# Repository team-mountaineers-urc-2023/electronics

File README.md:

# Electronics
This repository contains diagrams of Wanderer's electrical systems as well as PCBs designed by the Electronics sub-team.

# Table of Contents
[Downloading the Repository](#downloading-the-repository)   
[Required Software](#required-software)  
[Repository Contents](#repository-contents)  

# Downloading the Repository
## Pre-Install: SSH Key
An ssh key for your current machine must be added to your Github account to clone our repositories.  
SSH keys are used for passwordless authentication.  
For more information see https://docs.github.com/en/authentication/connecting-to-github-with-ssh.

## Creating an SSh Key
`$ ssh-keygen`  
Keep the default file name, add a password if you'd like. 

## Adding the SSH Key to your Github account
Go to https://github.com/settings/keys and click "New SSH Key"  
The title can be anything.  
For Key, copy paste the output of `$ cat ~/.ssh/id_rsa.pub`

## Clone the workspace
Install git if not done so already with `$ sudo apt install git` then:  
`git clone git@github.com:team-mountaineers-urc-2023/electronics.git ~electronics`
* If this is your first time talking to Github on your machine, you will receive a warning saying authenticity cannot be established.  
	Type "yes" and hit enter.

# Required Software
Block diagrams and schematics can be viewed using any PDF viewer.
All PCBs were designed using KiCad 7.0. The most recent version of the software can be downloaded at https://www.kicad.org/download/.

# Repository Contents

## System Schematics

Main Electronics Box Diagram

Manipulator Electronics Diagram

Science Electronics Diagram

## PCB Files

Battery Monitor v1.2

Payload PCB v3.1

Power Distribution Board

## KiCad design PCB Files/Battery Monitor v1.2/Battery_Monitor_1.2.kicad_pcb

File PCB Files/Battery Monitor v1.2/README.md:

# Battery Monitor v1.2

## Overview
The battery monitor was designed for the 2023 rover to monitor its battery usage. The PCB features shunt resistors to measure the current draw from up to four batteries. It can communicate status using an LCD screen or over the rover's CAN bus.

## Features
- 4-layer board
- Raspberry Pi Pico microcontroller
- Measures battery voltage and current using shunt resistors combined with LTC4151 ICs
- Embedded emergency stop circuitry
- Ideal diode circuits to connect batteries in parallel
- Control for an external LCD screen and an LED strip
- Hardware for CAN bus communication
- Reverse polarity protection

## Contributors
- [Kendra Gillo](https://github.com/kgillo)

- [Zach Waddell](https://github.com/zmw0006)

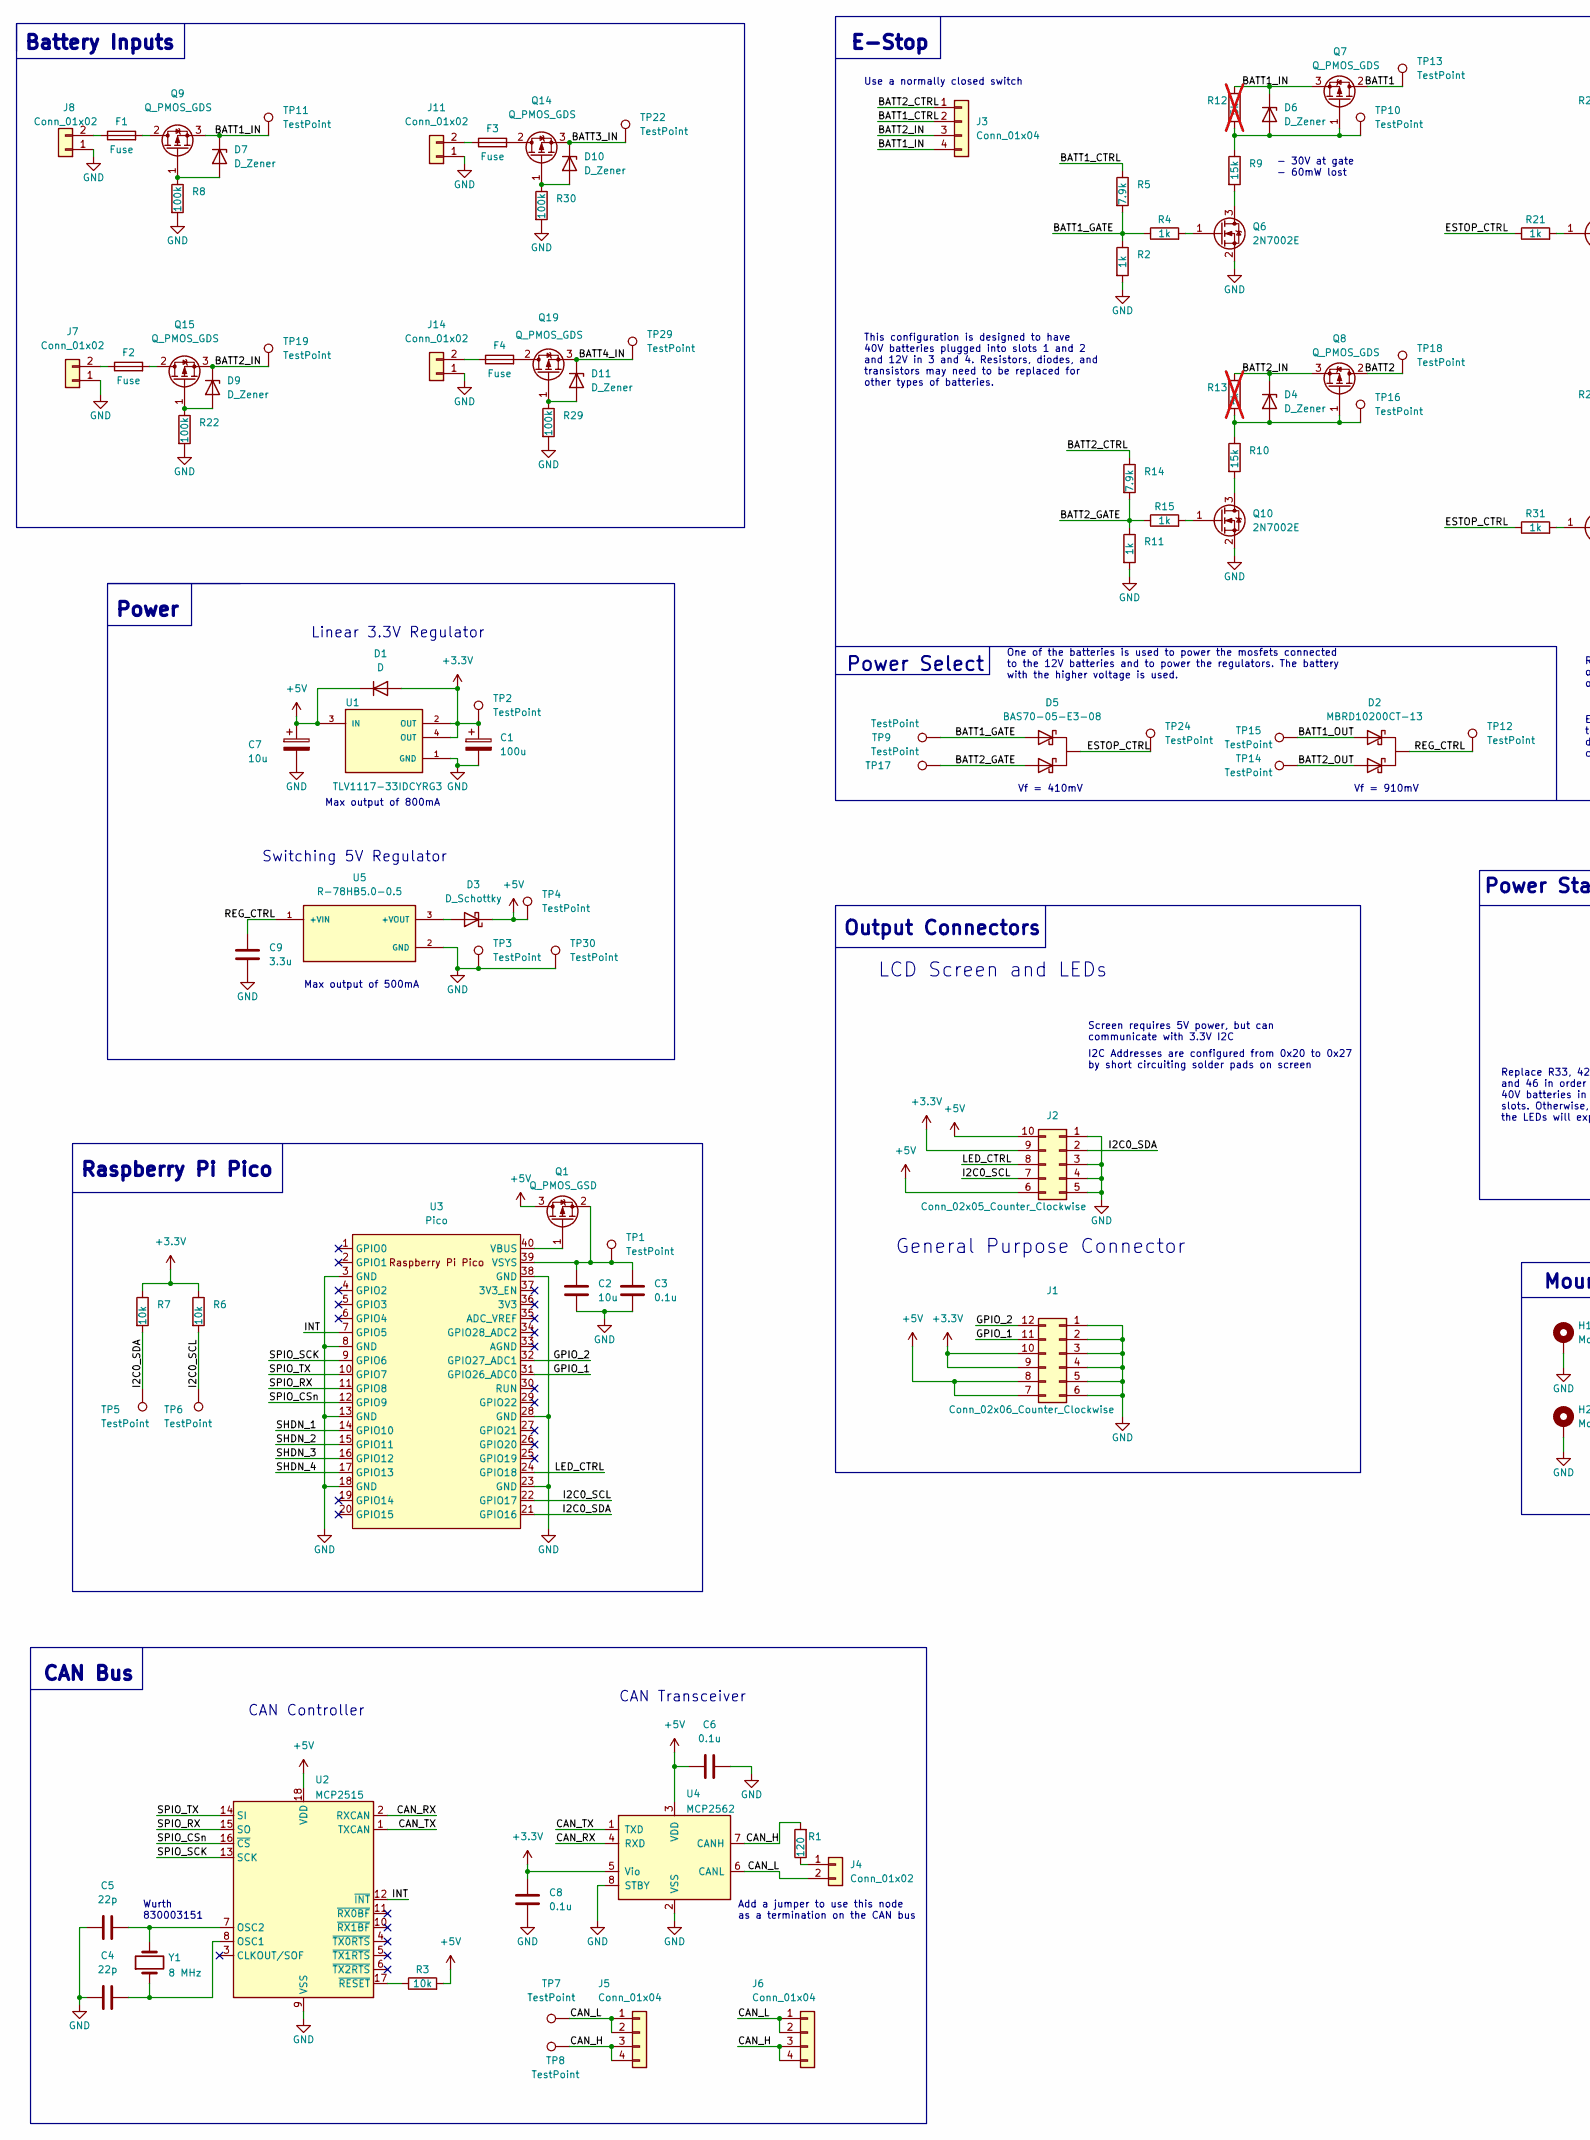
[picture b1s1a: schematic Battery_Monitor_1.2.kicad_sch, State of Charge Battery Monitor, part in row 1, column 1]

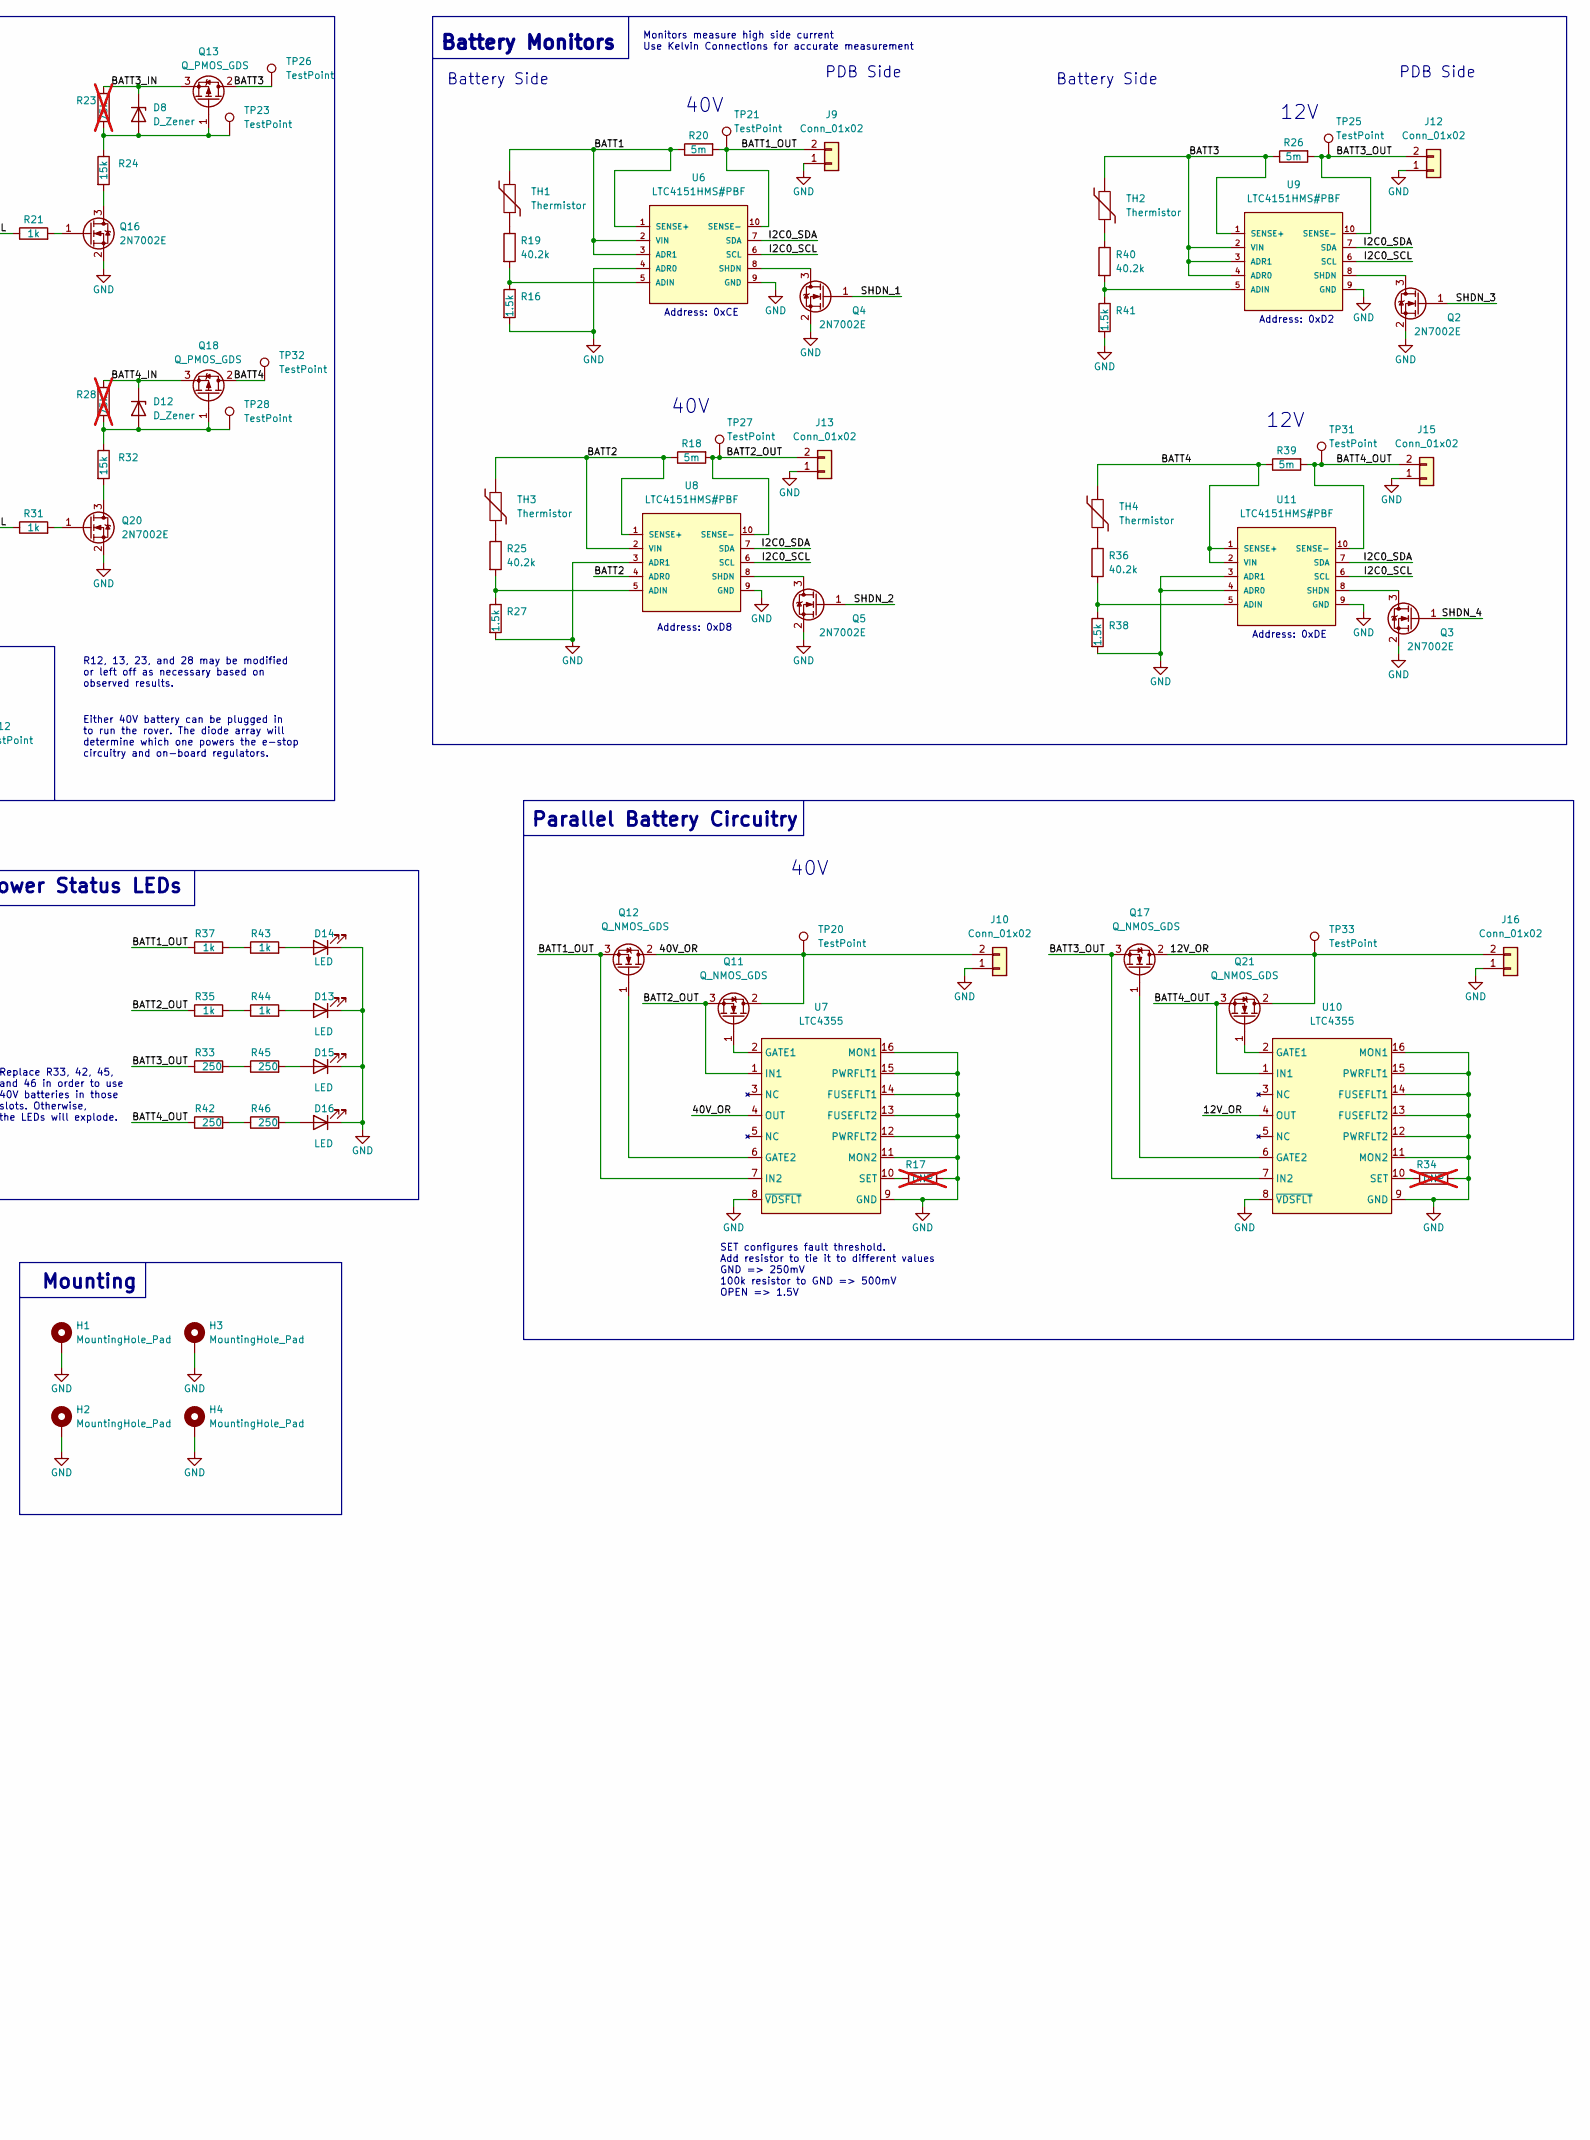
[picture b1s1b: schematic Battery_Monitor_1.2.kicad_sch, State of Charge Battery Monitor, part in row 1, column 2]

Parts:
C1: 100u; 1411 (3528 Metric)
C2, C7: 10u; C_0805_2012Metric_Pad1.18x1.45mm_HandSolder
C3: 0.1u; C_1206_3216Metric_Pad1.33x1.80mm_HandSolder
C4, C5: 22p; C_0603_1608Metric_Pad1.08x0.95mm_HandSolder
C6, C8: 0.1u; C_1206_3216Metric_Pad1.33x1.80mm_HandSolder; MANUFACTURER_PART_NUMBER 1206B104J500CT
C9: 3.3u; C_1812_4532Metric_Pad1.57x3.40mm_HandSolder
D1: D; SOD123FL3; MANUFACTURER_PART_NUMBER GS1001FL_R1_00001
D2: MBRD10200CT-13; TO-252-2; MANUFACTURER_PART_NUMBER MBRD10200CT-13
D3: D_Schottky; D_SOD-323; MANUFACTURER_PART_NUMBER CUS08F30,H3F
D4, D6, D7, D8, D9, D10, D11, D12: D_Zener; D_SOD-123; MANUFACTURER_PART_NUMBER BZT52C10-TP
D5: BAS70-05-E3-08; SOT-23; MANUFACTURER_PART_NUMBER BAS70-05-E3-08
D13, D14, D15, D16: LED; D_0805_2012Metric_Pad1.15x1.40mm_HandSolder; MANUFACTURER_PART_NUMBER LTST-C171GKT
F1, F2, F3, F4: Fuse; FUSE_3568
H1, H2, H3, H4: MountingHole_Pad; MountingHole_3.2mm_M3_DIN965_Pad
J1: Conn_02x06_Counter_Clockwise; Molex_Mini-Fit_Jr_5566-12A_2x06_P4.20mm_Vertical; MANUFACTURER_PART_NUMBER 0039281123
J2: Conn_02x05_Counter_Clockwise; Molex_Mini-Fit_Jr_5566-10A_2x05_P4.20mm_Vertical
J3: Conn_01x04; Molex_Mega-Fit_76829-0104_2x02_P5.70mm_Vertical; MANUFACTURER_PART_NUMBER 76829-0104
J4: Conn_01x02; PinHeader_1x02_P2.54mm_Vertical
J5, J6: Conn_01x04; 2604-3102; MANUFACTURER_PART_NUMBER 2604-3102
J7, J8, J9, J10, J11, J12, J13, J14, J15, J16: Conn_01x02; MOLEX_768290102; MANUFACTURER_PART_NUMBER 768290102
Q1: Q_PMOS_GSD; SOT-23; MANUFACTURER_PART_NUMBER DMG2305UX-13
Q2, Q3, Q4, Q5, Q6, Q10, Q16, Q20: 2N7002E; SOT-23; MANUFACTURER_PART_NUMBER 2N7002E
Q7, Q8, Q9, Q13, Q14, Q15, Q18, Q19: Q_PMOS_GDS; TO-252-2; MANUFACTURER_PART_NUMBER SUD50P10-43L-GE3
Q11, Q12, Q17, Q21: Q_NMOS_GDS; TO-252-2; MANUFACTURER_PART_NUMBER FDD86367
R1: 120; R_0805_2012Metric_Pad1.20x1.40mm_HandSolder; MANUFACTURER_PART_NUMBER CFR25SJT-52-120R
R2, R4, R11, R15, R21, R31, R35, R37, R43, R44: 1k; R_0805_2012Metric_Pad1.20x1.40mm_HandSolder
R3, R6, R7: 10k; R_0805_2012Metric_Pad1.20x1.40mm_HandSolder; MANUFACTURER_PART_NUMBER RNCP0805FTD10K0
R5, R14: 7.9k; R_0805_2012Metric_Pad1.20x1.40mm_HandSolder
R8, R22, R29, R30: 100k; R_0805_2012Metric_Pad1.20x1.40mm_HandSolder
R9, R10, R24, R32: 15k; R_0805_2012Metric_Pad1.20x1.40mm_HandSolder
R12, R13: 5k; R_0805_2012Metric_Pad1.20x1.40mm_HandSolder; not fitted
R16, R27, R38, R41: 1.5k; R_0805_2012Metric_Pad1.20x1.40mm_HandSolder
R17, R34: DNP; R_0805_2012Metric_Pad1.20x1.40mm_HandSolder; not fitted
R18, R20, R26, R39: 5m; SMT-R005-1.0; MANUFACTURER_PART_NUMBER SMT-R005-1.0
R19, R25, R36, R40: 40.2k; R_0805_2012Metric_Pad1.20x1.40mm_HandSolder
R23, R28: 75k; R_0805_2012Metric_Pad1.20x1.40mm_HandSolder; not fitted
R33, R42, R45, R46: 250; R_0805_2012Metric_Pad1.20x1.40mm_HandSolder
TH1, TH2, TH3, TH4: Thermistor; R_0603_1608Metric_Pad0.98x0.95mm_HandSolder; MANUFACTURER_PART_NUMBER NTCS0603E3104GXT
TP1, TP9, TP10, TP11, TP12, TP13, TP14, TP15, TP16, TP17, TP18, TP19, TP20, TP21, TP22, TP23, TP24, TP25, TP26, TP27, TP28, TP29, TP31, TP32, TP33: TestPoint; TestPoint_Pad_1.5x1.5mm
TP2, TP3, TP4, TP5, TP6, TP7, TP8, TP30: TestPoint; TestPoint_THTPad_1.5x1.5mm_Drill0.7mm
U1: TLV1117-33IDCYRG3; SOT-223; MANUFACTURER_PART_NUMBER TLV1117-33IDCYRG3
U2: MCP2515; SOIC-18W_7.5x11.6mm_P1.27mm; MANUFACTURER_PART_NUMBER MCP2515
U3: Pico; RPi_Pico_SMD_TH; MANUFACTURER_PART_NUMBER SC0915
U4: MCP2562; SOIC-8_3.9x4.9mm_P1.27mm; MANUFACTURER_PART_NUMBER MCP2562
U5: R-78HB5.0-0.5; CONV_R-78HB5.0-0.5; MANUFACTURER_PART_NUMBER R-78HB5.0-0.5
U6, U8, U9, U11: LTC4151HMS#PBF; MSOP-10_3x3mm_P0.5mm; MANUFACTURER_PART_NUMBER LTC4151HMS#PBF
U7, U10: LTC4355; MSOP-16_3x4.039mm_P0.5mm; MANUFACTURER_PART_NUMBER LTC4355
Y1: 8 MHz; Crystal_SMD_HC49-SD; MANUFACTURER_PART_NUMBER 830003151

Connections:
+3.3V: C1.1, C8.1, D1.2 (A), J1.9, J1.10, J2.9, R6.1, R7.1, TP2.1, U1.2 (OUT), U1.4 (OUT), U4.5 (Vio)
+5V: C6.1, C7.1, D1.1 (K), D3.1 (K), J1.7, J1.8, J2.6, J2.10, Q1.3 (D), R3.2, TP4.1, U1.3 (IN), U2.18 (VDD), U4.3 (VDD)
/12V_OR: J16.2, Q17.2 (D), Q21.2 (D), TP33.1, U10.4 (OUT)
/40V_OR: J10.2, Q11.2 (D), Q12.2 (D), TP20.1, U7.4 (OUT)
/BATT1: Q7.2 (D), R20.1, TH1.2, TP13.1, U6.1 (SENSE+), U6.2 (VIN), U6.3 (ADR1)
/BATT1_CTRL: J3.2, R5.1
/BATT1_GATE: D5.1 (A), R2.1, R4.1, R5.2, TP9.1
/BATT1_IN: D6.1 (K), D7.1 (K), J3.4, Q7.3 (S), Q9.3 (S), R12.1, TP11.1
/BATT1_OUT: D2.1 (A), J9.2, Q12.3 (S), R20.2, R37.1, TP15.1, TP21.1, U6.10 (SENSE-), U7.7 (IN2)
/BATT2: Q8.2 (D), R18.1, TH3.2, TP18.1, U8.1 (SENSE+), U8.2 (VIN), U8.4 (ADR0)
/BATT2_CTRL: J3.1, R14.1
/BATT2_GATE: D5.2 (A), R11.1, R14.2, R15.1, TP17.1
/BATT2_IN: D4.1 (K), D9.1 (K), J3.3, Q8.3 (S), Q15.3 (S), R13.1, TP19.1
/BATT2_OUT: D2.3 (A), J13.2, Q11.3 (S), R18.2, R35.1, TP14.1, TP27.1, U7.1 (IN1), U8.10 (SENSE-)
/BATT3: Q13.2 (D), R26.1, TH2.2, TP26.1, U9.1 (SENSE+), U9.2 (VIN), U9.3 (ADR1), U9.4 (ADR0)
/BATT3_IN: D8.1 (K), D10.1 (K), Q13.3 (S), Q14.3 (S), R23.1, TP22.1
/BATT3_OUT: J12.2, Q17.3 (S), R26.2, R33.1, TP25.1, U9.10 (SENSE-), U10.7 (IN2)
/BATT4: Q18.2 (D), R39.1, TH4.2, TP32.1, U11.1 (SENSE+), U11.2 (VIN)
/BATT4_IN: D11.1 (K), D12.1 (K), Q18.3 (S), Q19.3 (S), R28.1, TP29.1
/BATT4_OUT: J15.2, Q21.3 (S), R39.2, R42.1, TP31.1, U10.1 (IN1), U11.10 (SENSE-)
/CAN_H: J5.3, J5.4, J6.3, J6.4, R1.2, TP8.1, U4.7 (CANH)
/CAN_L: J4.2, J5.1, J5.2, J6.1, J6.2, TP7.1, U4.6 (CANL)
/CAN_RX: U2.2 (RXCAN), U4.4 (RXD)
/CAN_TX: U2.1 (TXCAN), U4.1 (TXD)
/ESTOP_CTRL: D5.3 (K), R21.1, R31.1, TP24.1
/GPIO_1: J1.11, U3.31 (GPIO26_ADC0)
/GPIO_2: J1.12, U3.32 (GPIO27_ADC1)
/I2C0_SCL: J2.7, R6.2, TP6.1, U3.22 (GPIO17), U6.6 (SCL), U8.6 (SCL), U9.6 (SCL), U11.6 (SCL)
/I2C0_SDA: J2.2, R7.2, TP5.1, U3.21 (GPIO16), U6.7 (SDA), U8.7 (SDA), U9.7 (SDA), U11.7 (SDA)
/INT: U2.12 (~INT), U3.7 (GPIO5)
/LED_CTRL: J2.8, U3.24 (GPIO18)
/REG_CTRL: C9.1, D2.2 (K), TP12.1, U5.1 (+VIN)
/SHDN_1: Q4.1 (G), U3.14 (GPIO10)
/SHDN_2: Q5.1 (G), U3.15 (GPIO11)
/SHDN_3: Q2.1 (G), U3.16 (GPIO12)
/SHDN_4: Q3.1 (G), U3.17 (GPIO13)
/SPIO_CSn: U2.16 (~CS), U3.12 (GPIO9)
/SPIO_RX: U2.15 (SO), U3.11 (GPIO8)
/SPIO_SCK: U2.13 (SCK), U3.9 (GPIO6)
/SPIO_TX: U2.14 (SI), U3.10 (GPIO7)
GND: C1.2, C2.1, C3.1, C4.1, C5.1, C6.2, C7.2, C8.2, C9.2, D13.1 (K), D14.1 (K), D15.1 (K), D16.1 (K), H1.1, H2.1, H3.1, H4.1, J1.1, J1.2, J1.3, J1.4, J1.5, J1.6, J2.1, J2.3, J2.4, J2.5, J7.1, J8.1, J9.1, J10.1, J11.1, J12.1, J13.1, J14.1, J15.1, J16.1, Q2.2 (S), Q3.2 (S), Q4.2 (S), Q5.2 (S), Q6.2 (S), Q10.2 (S), Q16.2 (S), Q20.2 (S), R2.2, R8.2, R11.2, R16.2, R17.2, R22.2, R27.2, R29.2, R30.2, R34.2, R38.2, R41.2, TP3.1, TP30.1, U1.1 (GND), U2.9 (VSS), U3.3 (GND), U3.8 (GND), U3.13 (GND), U3.18 (GND), U3.23 (GND), U3.28 (GND), U3.38 (GND), U4.2 (VSS), U4.8 (STBY), U5.2 (GND), U6.4 (ADR0), U6.9 (GND), U7.8 (~VDSFLT), U7.9 (GND), U7.11 (MON2), U7.12 (PWRFLT2), U7.13 (FUSEFLT2), U7.14 (FUSEFLT1), U7.15 (PWRFLT1), U7.16 (MON1), U8.3 (ADR1), U8.9 (GND), U9.9 (GND), U10.8 (~VDSFLT), U10.9 (GND), U10.11 (MON2), U10.12 (PWRFLT2), U10.13 (FUSEFLT2), U10.14 (FUSEFLT1), U10.15 (PWRFLT1), U10.16 (MON1), U11.3 (ADR1), U11.4 (ADR0), U11.9 (GND)
unnamed: D3.2 (A), U5.3 (+VOUT)
unnamed: D4.2 (A), Q8.1 (G), R10.1, R13.2, TP16.1
unnamed: D6.2 (A), Q7.1 (G), R9.1, R12.2, TP10.1
unnamed: D7.2 (A), Q9.1 (G), R8.1
unnamed: D8.2 (A), Q13.1 (G), R23.2, R24.1, TP23.1
unnamed: D9.2 (A), Q15.1 (G), R22.1
unnamed: D10.2 (A), Q14.1 (G), R30.1
unnamed: D11.2 (A), Q19.1 (G), R29.1
unnamed: D12.2 (A), Q18.1 (G), R28.2, R32.1, TP28.1
unnamed: D13.2 (A), R44.2
unnamed: D14.2 (A), R43.2
unnamed: D15.2 (A), R45.2
unnamed: D16.2 (A), R46.2
unnamed: J4.1, R1.1
unnamed: F2.1, J7.2
unnamed: F1.1, J8.2
unnamed: F3.1, J11.2
unnamed: F4.1, J14.2
unnamed: Q1.1 (G), U3.40 (VBUS)
unnamed: C2.2, C3.2, Q1.2 (S), TP1.1, U3.39 (VSYS)
unnamed: Q2.3 (D), U9.8 (SHDN)
unnamed: Q3.3 (D), U11.8 (SHDN)
unnamed: Q4.3 (D), U6.8 (SHDN)
unnamed: Q5.3 (D), U8.8 (SHDN)
unnamed: Q6.3 (D), R9.2
unnamed: Q6.1 (G), R4.2
unnamed: F1.2, Q9.2 (D)
unnamed: Q10.3 (D), R10.2
unnamed: Q10.1 (G), R15.2
unnamed: Q11.1 (G), U7.2 (GATE1)
unnamed: Q12.1 (G), U7.6 (GATE2)
unnamed: F3.2, Q14.2 (D)
unnamed: F2.2, Q15.2 (D)
unnamed: Q16.3 (D), R24.2
unnamed: Q16.1 (G), R21.2
unnamed: Q17.1 (G), U10.6 (GATE2)
unnamed: F4.2, Q19.2 (D)
unnamed: Q20.3 (D), R32.2
unnamed: Q20.1 (G), R31.2
unnamed: Q21.1 (G), U10.2 (GATE1)
unnamed: R19.1, TH1.1
unnamed: R25.1, TH3.1
unnamed: R33.2, R45.1
unnamed: R35.2, R44.1
unnamed: R36.1, TH4.1
unnamed: R37.2, R43.1
unnamed: R40.1, TH2.1
unnamed: R42.2, R46.1
unnamed: C4.2, U2.8 (OSC1), Y1.1
unnamed: C5.2, U2.7 (OSC2), Y1.2
unnamed: R3.1, U2.17 (~RESET)
unnamed: R16.1, R19.2, U6.5 (ADIN)
unnamed: R17.1, U7.10 (SET)
unnamed: R25.2, R27.1, U8.5 (ADIN)
unnamed: R40.2, R41.1, U9.5 (ADIN)
unnamed: R34.1, U10.10 (SET)
unnamed: R36.2, R38.1, U11.5 (ADIN)

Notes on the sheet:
One of the batteries is used to power the mosfets connected to the 12V batteries and to power the regulators. The battery with the higher voltage is used.
Either 40V battery can be plugged in to run the rover. The diode array will determine which one powers the e-stop circuitry and on-board regulators.
40V
- 30V at gate - 60mW lost
SET configures fault threshold. Add resistor to tie it to different values GND => 250mV 100k resistor to GND => 500mV OPEN => 1.5V
Wurth 830003151
Power
CAN Transceiver
Replace R33, 42, 45, and 46 in order to use 40V batteries in those slots. Otherwise, the LEDs will explode.
Address: 0xD8
Address: 0xD2
Power Select
CAN Bus
This configuration is designed to have 40V batteries plugged into slots 1 and 2 and 12V in 3 and 4. Resistors, diodes, and transistors may need to be replaced for other types of batteries.
Max output of 500mA
Max output of 800mA
Add a jumper to use this node as a termination on the CAN bus
Address: 0xDE
Mounting
12V
Parallel Battery Circuitry
PDB Side
Raspberry Pi Pico
CAN Controller
Power Status LEDs
LCD Screen and LEDs
R12, 13, 23, and 28 may be modified or left off as necessary based on observed results.
Vf = 910mV
Monitors measure high side current Use Kelvin Connections for accurate measurement
I2C Addresses are configured from 0x20 to 0x27 by short circuiting solder pads on screen
Battery Side
Use a normally closed switch
Battery Inputs
Battery Monitors
E-Stop
Linear 3.3V Regulator
Screen requires 5V power, but can communicate with 3.3V I2C
Address: 0xCE
Vf = 410mV
General Purpose Connector

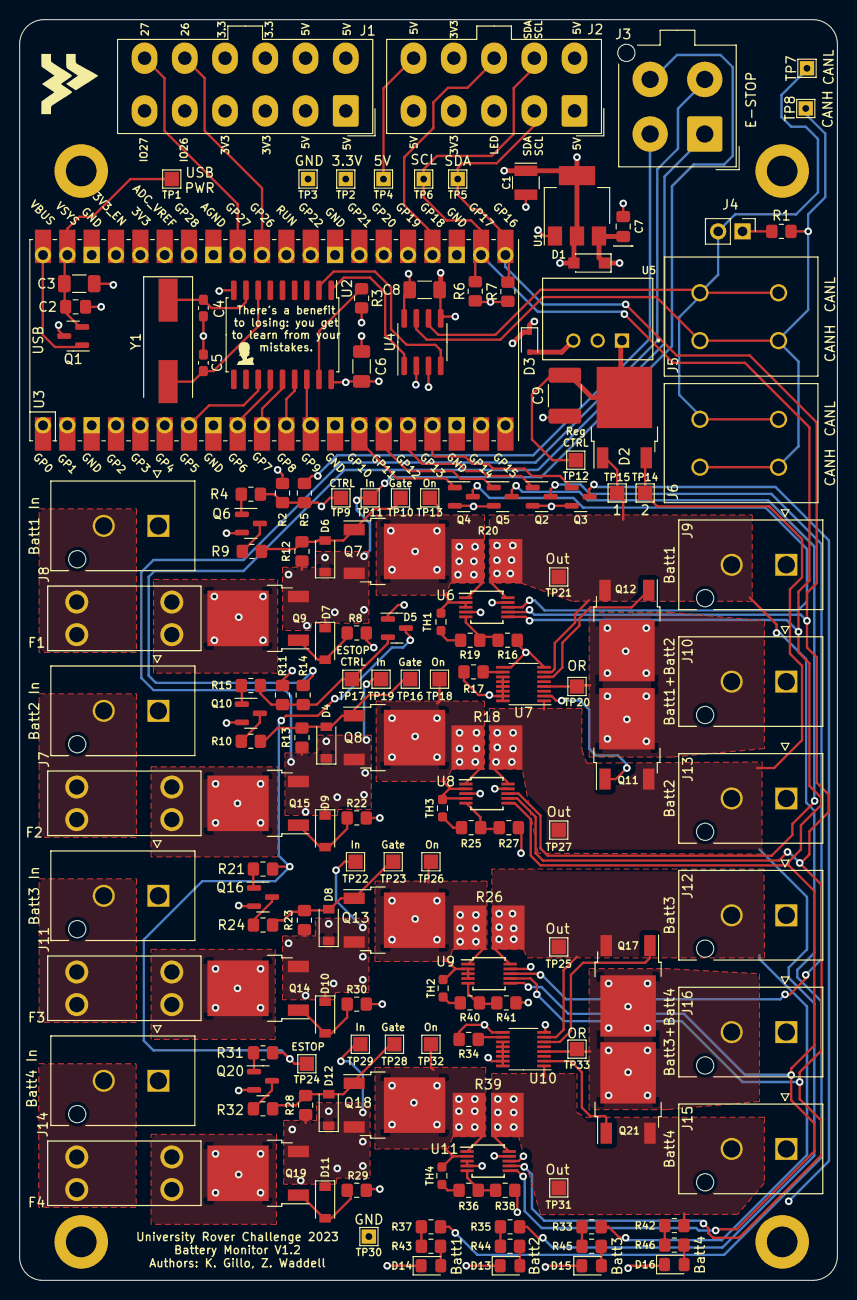
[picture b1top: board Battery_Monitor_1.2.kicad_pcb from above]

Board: 4 copper layers, 85.3 x 131.6 mm, 166 parts (0 on the bottom side), 98 nets.

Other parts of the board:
G1: LOGO; Flying_WV

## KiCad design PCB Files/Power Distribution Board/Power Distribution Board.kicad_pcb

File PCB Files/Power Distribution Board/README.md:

# Power Distribution Board

## Overview
The Power Distribution Board includes DC/DC converters used to step down the battery power to the necessary voltages needed throughout the rover. It can be populated with up to three 40 or 60W Traco Power DC/DC converters as well as two 20W regulators. It also includes integrated emergency stop circuitry and two pass-through power rails.

## Features
- 2-layer board
- Supports up to four batteries powering DC/DC converters
- Allows up to three 40W or 60W regulators
- Includes up to two 20W regulators
- Two pass-through voltage rails allowing unregulated power directly from batteries
- In-rush current limiters on drive motor connections
- Connectors have selectable outputs - jumpers determine which regulator they are attached to
- E-stop bypass allows the computer to remain powered when the emergency stop is used

## Contributors
- Scott Harper
- Conner Castle
- Yu Gu

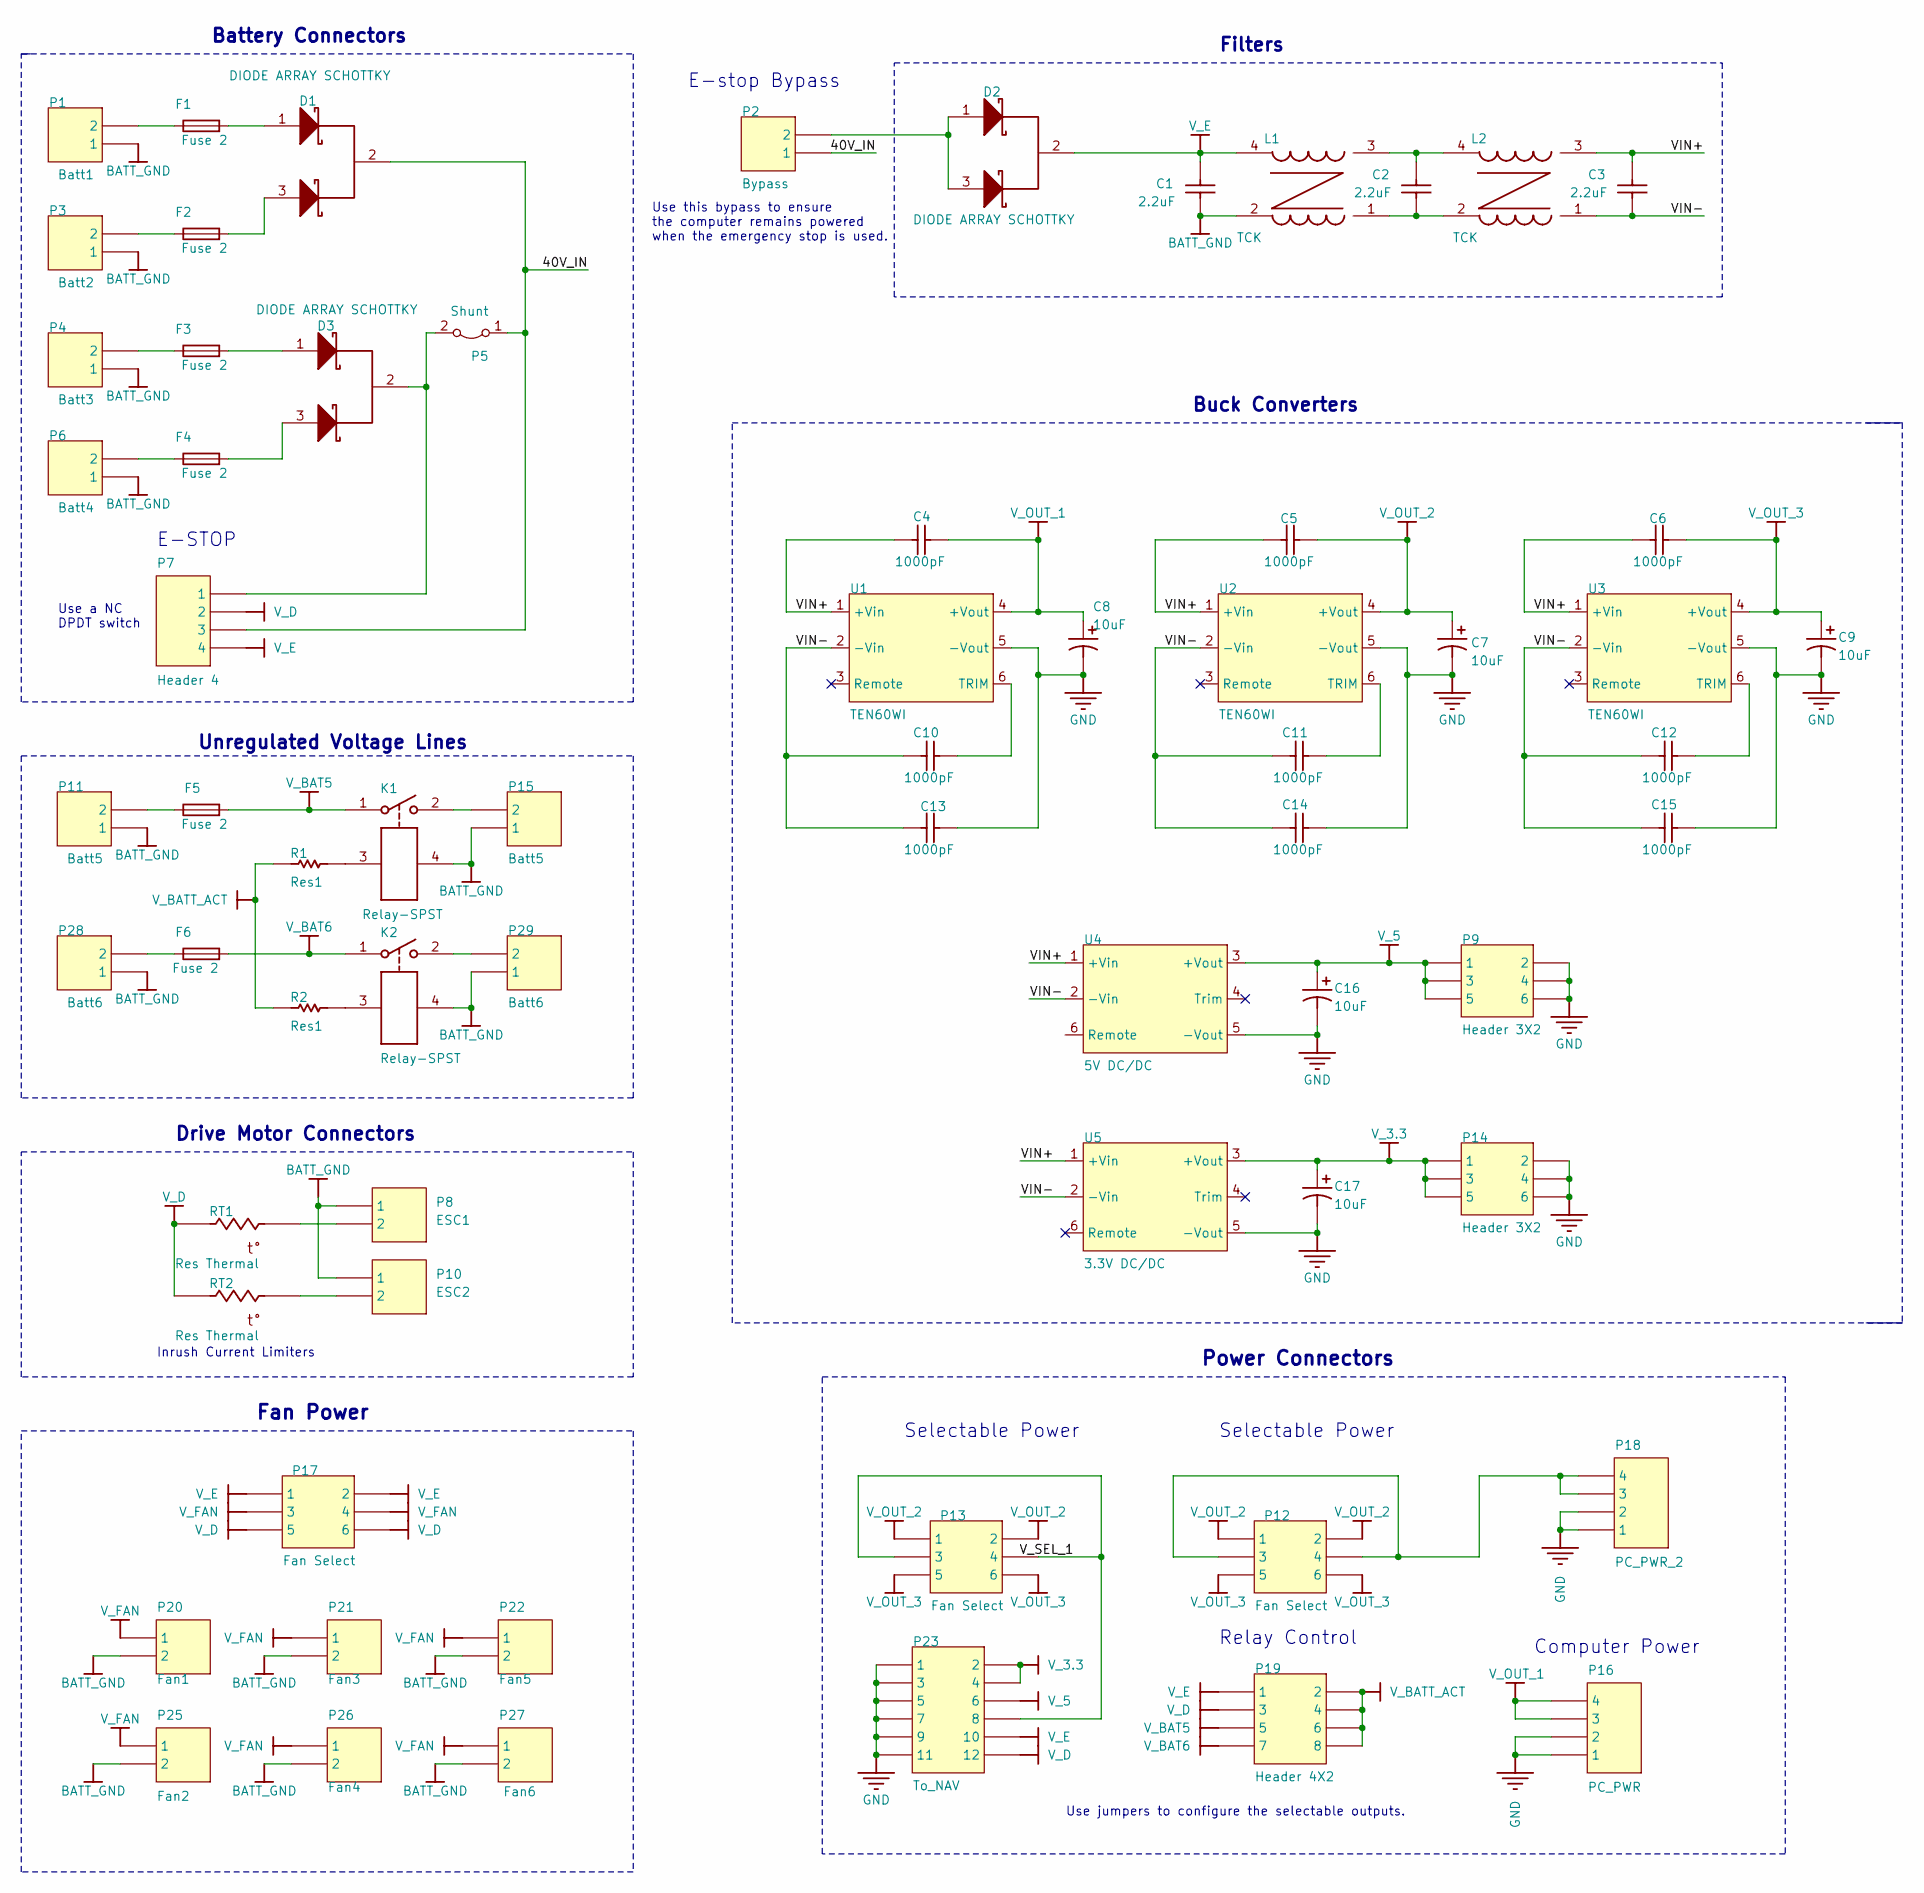
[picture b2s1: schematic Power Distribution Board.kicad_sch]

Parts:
C1, C2, C3: 2.2uF; SMD Cap
C4, C5, C6, C10, C11, C12, C13, C14, C15: 1000pF; SMD Cap
C7, C8, C9, C16, C17: 10uF; SMD Cap Pol
D1, D2, D3: DIODE ARRAY SCHOTTKY; D2PAK3; Part Number MBRB20200CTT4G
F1, F2, F3, F4, F5, F6: Fuse 2; FuseHolder_2; Part Number 3568
K1, K2: Relay-SPST; Relay Socket; Part Number JW1-PS and JW1FSN-DC48V
L1: TCK; TCK Choke; Part Number TCK-053
L2: TCK; TCK Choke; Part Number TCK-076
P1: Batt1; MEGAFIT 2 RA; Part Number 1720641002
P2: Bypass; MEGAFIT 2 RA; Part Number 1720641002
P3: Batt2; MEGAFIT 2 RA; Part Number 1720641002
P4: Batt3; MEGAFIT 2 RA; Part Number 1720641002
P5: Shunt
P6: Batt4; MEGAFIT 2 RA; Part Number 1720641002
P7: Header 4; MEGAFIT 4 RA; Part Number 768250004
P8: ESC1; MEGAFIT 2 RA; Part Number 1720641002
P9, P14: Header 3X2; HDR2X3
P10: ESC2; MEGAFIT 2 RA; Part Number 1720641002
P11, P15: Batt5; MEGAFIT 2 RA; Part Number 1720641002
P12, P13, P17: Fan Select; HDR2X3
P16: PC_PWR; Minifit 4 RA; Part Number 26013115
P18: PC_PWR_2; Minifit 4 RA; Part Number 26013115
P19: Header 4X2; HDR2X4
P20: Fan1; 2 Pin Locking Shrouded Connector; Part Number 705430036
P21: Fan3; 2 Pin Locking Shrouded Connector; Part Number 705430036
P22: Fan5; 2 Pin Locking Shrouded Connector; Part Number 705430036
P23: To_NAV; Microfit 8; Part Number 430451200
P25: Fan2; 2 Pin Locking Shrouded Connector; Part Number 705430036
P26: Fan4; 2 Pin Locking Shrouded Connector; Part Number 705430036
P27: Fan6; 2 Pin Locking Shrouded Connector; Part Number 705430036
P28, P29: Batt6; MEGAFIT 2 RA; Part Number 1720641002
R1, R2: Res1; AXIAL-0.3
RT1, RT2: Res Thermal; ICL; Part Number SL12 1R010
U1, U2, U3: TEN60WI; TEN 60WIN; Part Number TEN 60-4812WIN, TEN 40-1213E, or TEN 60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
U4: 5V DC/DC; THN 20WI; Part Number THN 30-4811WI
U5: 3.3V DC/DC; THN 20WI; Part Number THN 30-4810WI

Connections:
/40V_IN: D1.2 (A), P2.1, P5.1 (A), P7.3
/VIN+: C3.1, C4.2, C5.2, C6.2, L2.3 (1), U1.1 (+Vin), U2.1 (+Vin), U3.1 (+Vin), U4.1 (+Vin), U5.1 (+Vin)
/VIN-: C3.2, C10.2, C11.2, C12.2, C13.2, C14.2, C15.2, L2.1, U1.2 (-Vin), U2.2 (-Vin), U3.2 (-Vin), U4.2 (-Vin), U5.2 (-Vin)
/V_SEL_1: P13.3, P13.4, P23.8
BATT_GND: C1.2, K1.4, K2.4, L1.2, P1.1, P3.1, P4.1, P6.1, P8.1, P10.1, P11.1, P15.1, P20.2, P21.2, P22.2, P25.2, P26.2, P27.2, P28.1, P29.1
GND: C7.2, C8.2, C9.2, C13.1, C14.1, C15.1, C16.2, C17.2, P9.2, P9.4, P9.6, P14.2, P14.4, P14.6, P16.1, P16.2, P18.1, P18.2, P23.1, P23.3, P23.5, P23.7, P23.9, P23.11, U1.5 (-Vout), U2.5 (-Vout), U3.5 (-Vout), U4.5 (-Vout), U5.5 (-Vout)
unnamed: C2.1, L1.3 (1), L2.4 (2)
unnamed: C2.2, L1.1, L2.2
unnamed: D1.1 (A), F1.2
unnamed: D1.3 (A), F2.2
unnamed: D2.1 (A), D2.3 (A), P2.2
unnamed: D3.1 (A), F3.2
unnamed: D3.3 (A), F4.2
unnamed: F1.1, P1.2
unnamed: F2.1, P3.2
unnamed: F3.1, P4.2
unnamed: F4.1, P6.2
unnamed: F5.1, P11.2
unnamed: F6.1, P28.2
unnamed: K1.2, P15.2
unnamed: K1.3, R1.2
unnamed: K2.2, P29.2
unnamed: K2.3, R2.2
unnamed: D3.2 (A), P5.2 (B), P7.1
unnamed: P8.2, RT1.1
unnamed: P10.2, RT2.1
unnamed: P12.3, P12.4, P18.3, P18.4
unnamed: C10.1, U1.6 (TRIM)
unnamed: C11.1, U2.6 (TRIM)
unnamed: C12.1, U3.6 (TRIM)
V_3.3: C17.1, P14.1, P14.3, P14.5, P23.2, P23.4, U5.3 (+Vout)
V_5: C16.1, P9.1, P9.3, P9.5, P23.6, U4.3 (+Vout)
V_BAT5: F5.2, K1.1, P19.5
V_BAT6: F6.2, K2.1, P19.7
V_BATT_ACT: P19.2, P19.4, P19.6, P19.8, R1.1, R2.1
V_D: P7.2, P17.5, P17.6, P19.3, P23.12, RT1.2, RT2.2
V_E: C1.1, D2.2 (A), L1.4 (2), P7.4, P17.1, P17.2, P19.1, P23.10
V_FAN: P17.3, P17.4, P20.1, P21.1, P22.1, P25.1, P26.1, P27.1
V_OUT_1: C4.1, C8.1, P16.3, P16.4, U1.4 (+Vout)
V_OUT_2: C5.1, C7.1, P12.1, P12.2, P13.1, P13.2, U2.4 (+Vout)
V_OUT_3: C6.1, C9.1, P12.5, P12.6, P13.5, P13.6, U3.4 (+Vout)

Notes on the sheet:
Filters
Use this bypass to ensure the computer remains powered when the emergency stop is used.
Relay Control
Selectable Power
Unregulated Voltage Lines
Buck Converters
Inrush Current Limiters
E-STOP
Use jumpers to configure the selectable outputs.
Drive Motor Connectors
E-stop Bypass
Fan Power
Power Connectors
Use a NC DPDT switch
Battery Connectors
Computer Power

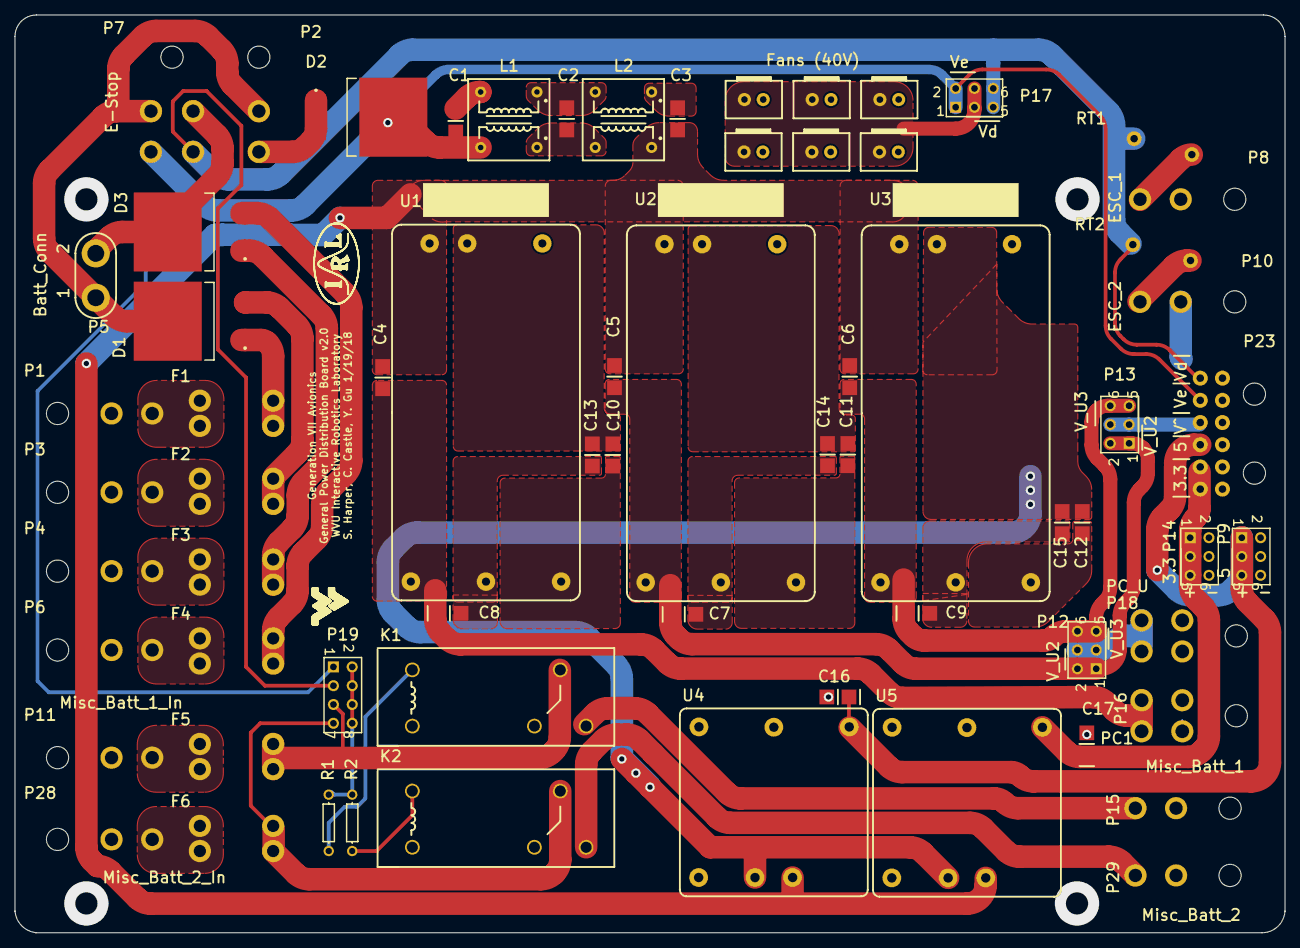
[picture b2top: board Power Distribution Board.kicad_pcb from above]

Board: 2 copper layers, 171.7 x 124.1 mm, 67 parts (0 on the bottom side), 41 nets.

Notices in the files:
parts and their libraries:
Copyright 2021 Accelerated Designs. All rights reserved.
